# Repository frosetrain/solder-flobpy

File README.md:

# Flobpy

I made a PCB that is the exact shape as a floppy disk, with some interactive components.

Slack username: `frosetrain`

Made for https://solder.hackclub.com

## Features

### Night light

The first LED lights up when the surrounding brightness is below a certain threshold. It uses a photoresistor and NPN transistor.

### Astable Multivibrator

This uses four resistors, two capacitors and two NPN transistors. This circuit makes the two LEDs flash in an alternating pattern. (I got this circuit idea from Falstad’s Circuit JS)

### Dimmable LED

It’s just a potentiometer.

### Motor disc

With the push of a button, the thing vibrates!

## The Story

I initially wanted to make a PCB in the shape of a floppy disk. To do this, I needed an accurate vector image of a floppy disk to add to KiCad. I could _not_ find one (everything online was a goofy emoji). So I painstakingly went through ECMA 147, the standard that defines floppy disks, and drew everything exactly in Inkscape.

For the logic, I was unfamiliar with how transistors worked, but thankfully Falstad’s Circuit JS allowed me to learn how it worked, and design my own circuit.

I decided to use a ground fill only on the back side. Maybe it should have been both sides.

I also added some lines to make it look like a floppy disk, and added some other text and images 👍

## Bill of Materials

- 1 battery holder
- 2 10µF capacitors
- 4 LEDs
- 1 mini motor disc
- 3 NPN transistors
- 3 220 resistors
- 2 4.7k resistors
- 3 47k resistors
- 1 potentiometer
- 1 LDR
- 2 push buttons

## Schematic

## PCB

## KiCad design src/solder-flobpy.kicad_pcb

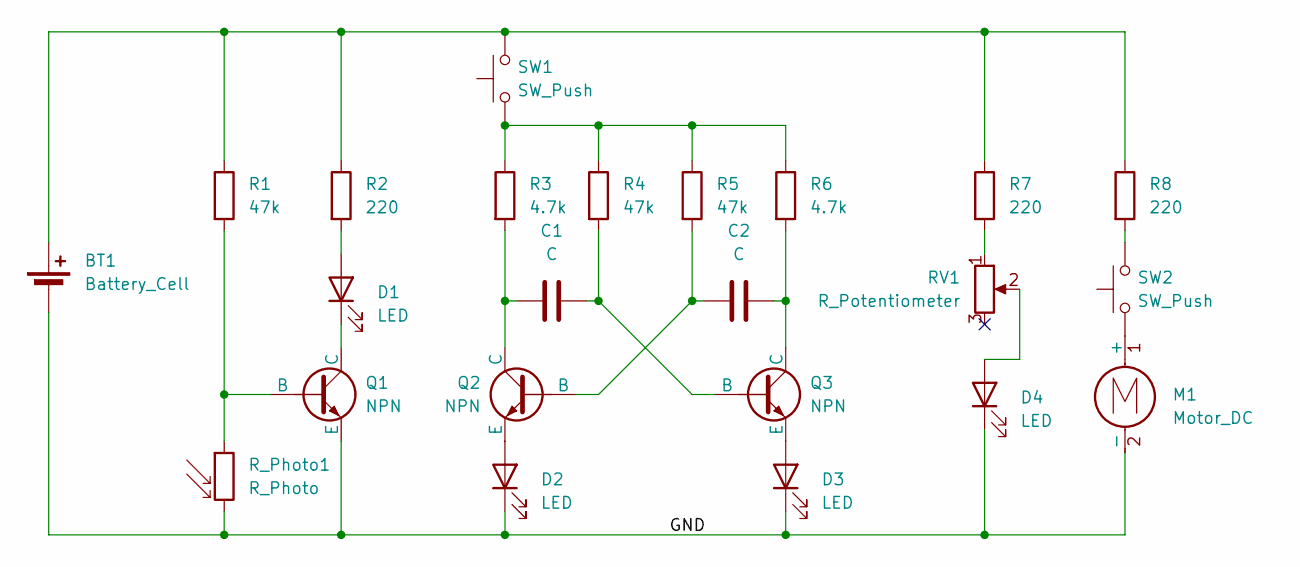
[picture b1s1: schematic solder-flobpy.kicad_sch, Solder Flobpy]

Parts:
BT1: Battery_Cell; BatteryHolder_Keystone_3034_1x20mm
C1, C2: C; C_Radial_D8.0mm_H7.0mm_P3.50mm
D1, D2, D3, D4: LED; LED_D5.0mm
M1: Motor_DC; PinHeader_1x02_P2.54mm_Vertical
Q1, Q2, Q3: NPN; TO-92_HandSolder
R1, R4, R5: 47k; R_Axial_DIN0207_L6.3mm_D2.5mm_P7.62mm_Horizontal
R2, R7, R8: 220; R_Axial_DIN0207_L6.3mm_D2.5mm_P7.62mm_Horizontal
R3, R6: 4.7k; R_Axial_DIN0207_L6.3mm_D2.5mm_P7.62mm_Horizontal
RV1: R_Potentiometer; Potentiometer_Vishay_T73YP_Vertical
R_Photo1: R_Photo; R_LDR_5.1x4.3mm_P3.4mm_Vertical
SW1, SW2: SW_Push; SW_PUSH_6mm

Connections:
/GND: BT1.2 (-), D2.1 (K), D3.1 (K), D4.1 (K), M1.2 (-), Q1.3 (E), R_Photo1.2
unnamed: BT1.1 (+), R1.1, R2.1, R7.1, R8.1, SW1.2
unnamed: D1.2 (A), R2.2
unnamed: D1.1 (K), Q1.1 (C)
unnamed: D2.2 (A), Q2.3 (E)
unnamed: D3.2 (A), Q3.3 (E)
unnamed: D4.2 (A), RV1.2
unnamed: M1.1 (+), SW2.1
unnamed: Q1.2 (B), R1.2, R_Photo1.1
unnamed: C2.1, Q2.2 (B), R5.2
unnamed: C1.1, Q2.1 (C), R3.2
unnamed: C1.2, Q3.2 (B), R4.2
unnamed: C2.2, Q3.1 (C), R6.2
unnamed: R3.1, R4.1, R5.1, R6.1, SW1.1
unnamed: R7.2, RV1.1
unnamed: R8.2, SW2.2

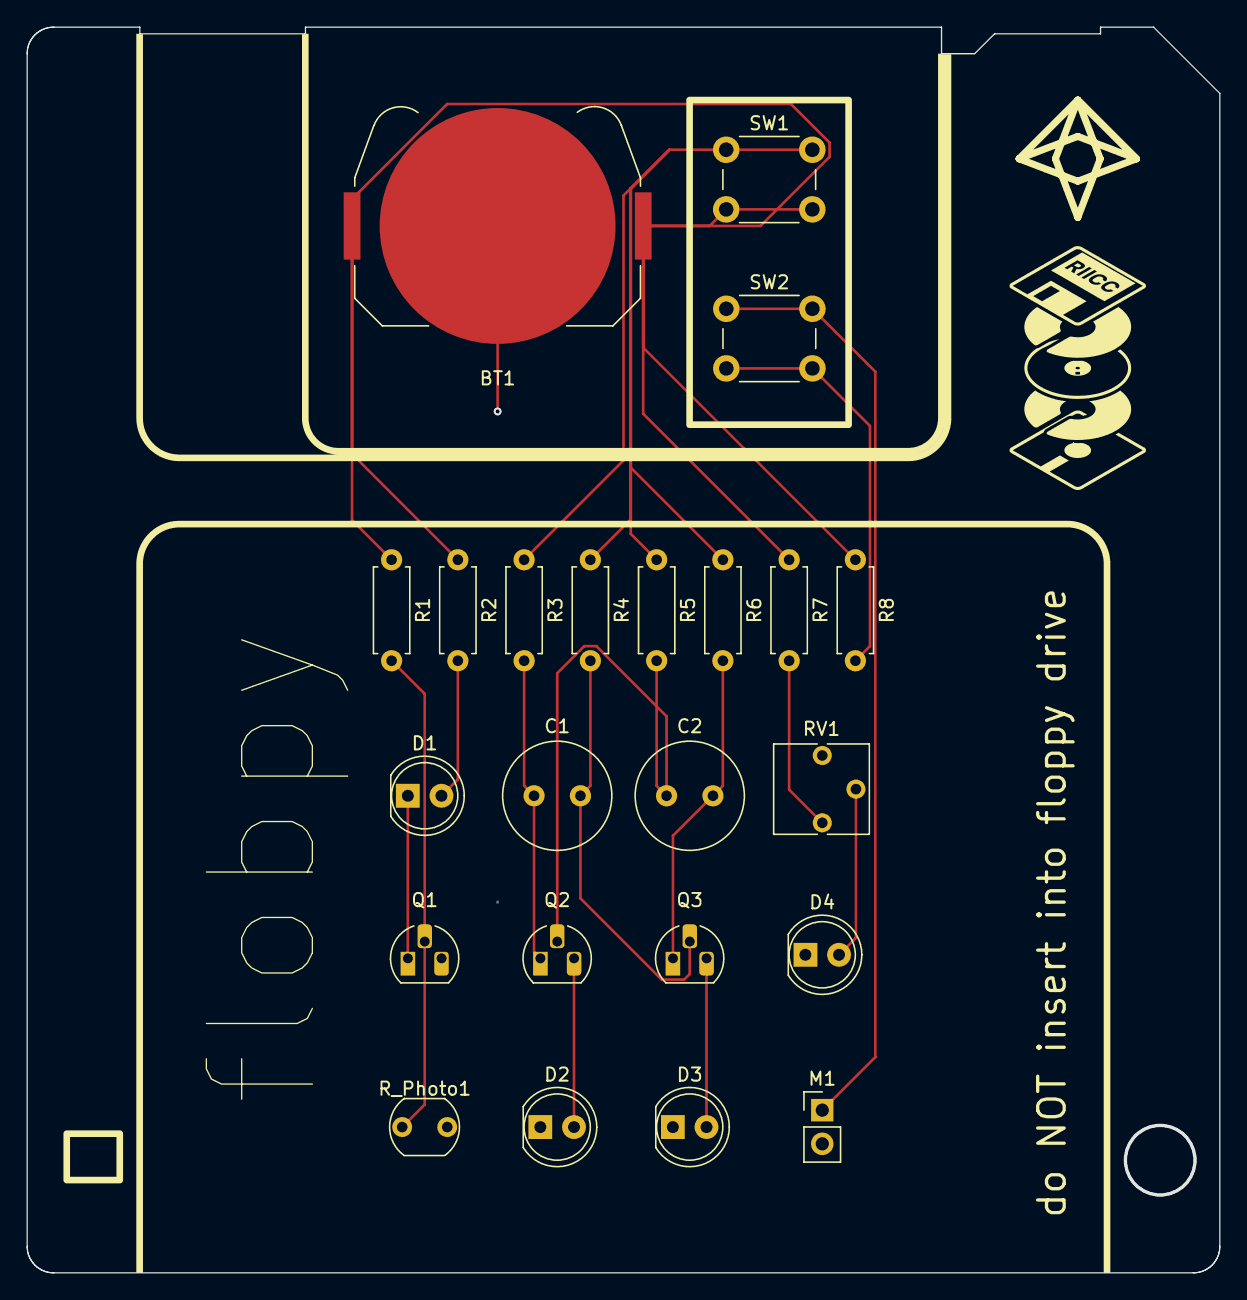
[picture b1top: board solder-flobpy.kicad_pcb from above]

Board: 2 copper layers, 90.0 x 94.0 mm, 23 parts (0 on the bottom side), 16 nets.

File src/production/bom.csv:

Designator,Footprint,Quantity,Value,LCSC Part #
BT1,BatteryHolder_Keystone_3034_1x20mm,1,Battery_Cell,
"C1, C2",C_Radial_D8.0mm_H7.0mm_P3.50mm,2,C,
"D1, D2, D3, D4",LED_D5.0mm,4,LED,
M1,PinHeader_1x02_P2.54mm_Vertical,1,Motor_DC,
"Q1, Q2, Q3",TO-92_HandSolder,3,NPN,
"R1, R4, R5",R_Axial_DIN0207_L6.3mm_D2.5mm_P7.62mm_Horizontal,3,47k,
"R2, R7, R8",R_Axial_DIN0207_L6.3mm_D2.5mm_P7.62mm_Horizontal,3,220,
"R3, R6",R_Axial_DIN0207_L6.3mm_D2.5mm_P7.62mm_Horizontal,2,4.7k,
RV1,Potentiometer_Vishay_T73YP_Vertical,1,R_Potentiometer,
R_PHOTO1,R_LDR_5.1x4.3mm_P3.4mm_Vertical,1,R_Photo,
"SW1, SW2",SW_PUSH_6mm,2,SW_Push,

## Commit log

2025-06-03 Add back silkscreen
2025-06-03 Add some more images
2025-06-03 Convert SVGs to PNGs
2025-06-03 Crop 3d_b
